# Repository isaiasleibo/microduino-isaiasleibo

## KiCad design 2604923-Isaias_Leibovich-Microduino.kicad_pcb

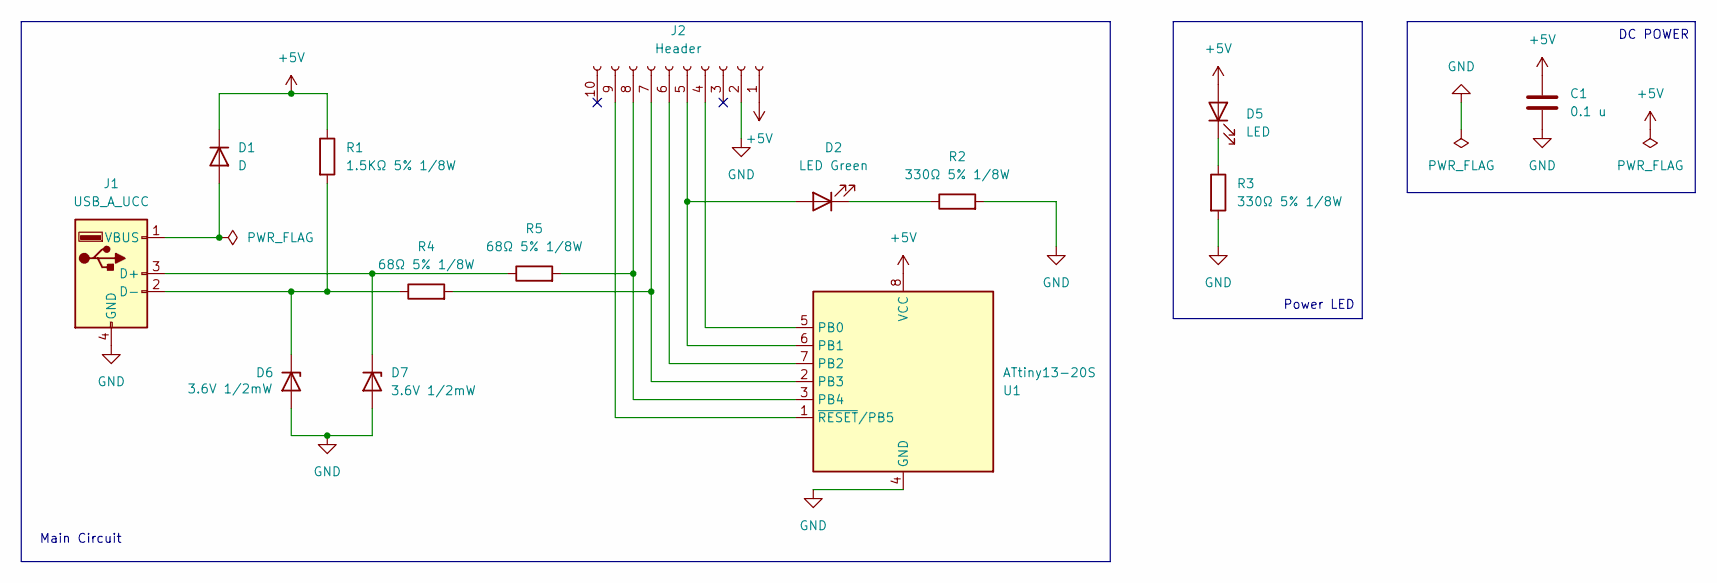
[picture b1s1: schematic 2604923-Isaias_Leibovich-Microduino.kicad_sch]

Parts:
C1: 0.1 u; C_0805_2012Metric_Pad1.18x1.45mm_HandSolder
D1: D; D_MELF_Handsoldering
D2: LED Green; LED.R-UCC
D5: LED; LED.R-UCC
D6, D7: 3.6V 1/2mW; D_SOD-123
J1: USB_A_UCC
J2: Header; PinSocket_1x10_P2.54mm_Vertical
R1: 1.5KΩ 5% 1/8W; R_0805_2012Metric_Pad1.20x1.40mm_HandSolder
R2, R3: 330Ω 5% 1/8W; R_0805_2012Metric_Pad1.20x1.40mm_HandSolder
R4, R5: 68Ω 5% 1/8W; R_0805_2012Metric_Pad1.20x1.40mm_HandSolder
U1: ATtiny13-20S; SOIC-8_5.3x5.3mm_P1.27mm

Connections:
+5V: C1.1, D1.1 (K), D5.2 (A), J2.1, R1.1, U1.8 (VCC)
GND: C1.2, D6.2 (A), D7.2 (A), J1.4 (GND), J2.2, R2.2, R3.2, U1.4 (GND)
unnamed: D1.2 (A), J1.1 (VBUS)
unnamed: D2.2 (A), J2.5, U1.6 (PB1)
unnamed: D2.1 (K), R2.1
unnamed: D5.1 (K), R3.1
unnamed: D6.1 (K), J1.2 (D-), R1.2, R4.1
unnamed: D7.1 (K), J1.3 (D+), R5.1
unnamed: J2.4, U1.5 (PB0)
unnamed: J2.6, U1.7 (PB2)
unnamed: J2.7, R4.2, U1.2 (PB3)
unnamed: J2.8, R5.2, U1.3 (PB4)
unnamed: J2.9, U1.1 (~RESET/PB5)

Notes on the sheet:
DC POWER
Power LED
Main Circuit

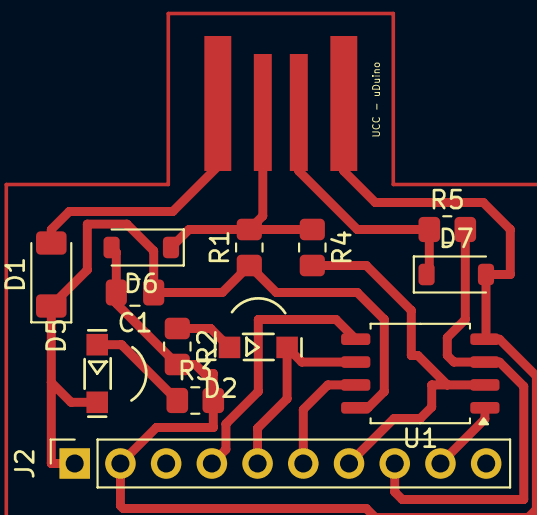
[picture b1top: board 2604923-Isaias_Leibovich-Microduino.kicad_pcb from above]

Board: 2 copper layers, 14 parts (0 on the bottom side), 13 nets.

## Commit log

2026-04-15 agregue las rutas en el pcb
